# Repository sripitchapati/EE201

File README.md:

# Keerthi Pitchapati
## About Me

Hi! My name is Sri Keerthi Pitchapati. I am currently a junior studying Electrical and Computer Engineering. 
Apart from this class, I'm taking EE 242, EE 215, CEE 291, and Engr 321. In this class, I'm most excited to 
learn things that I feel will be incredibly applicable to anything that I will do in the future

Apart from school, I have an internship with a company called Slice. Slice is a pizza delivery place that focuses 
local pizzerias, and giving them a platform to sell pizza online. 

Some of my hobbies include going to the gym, skiing, and reading. I ski almost every weekend and I enjoy meeting people
with this shared interest. In addition, I go to the gym almost every day. I also read often and enjoy science fiction.

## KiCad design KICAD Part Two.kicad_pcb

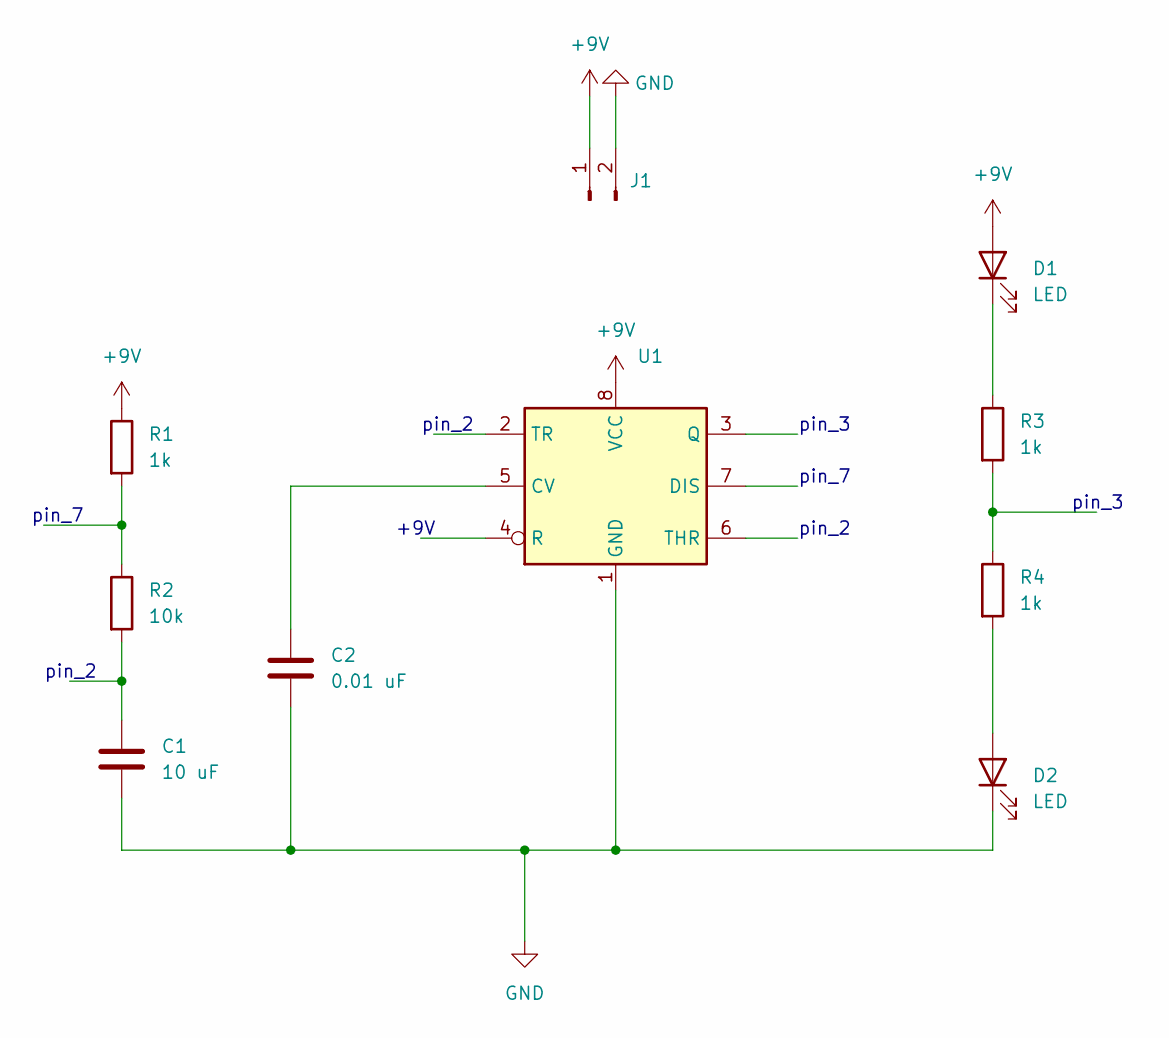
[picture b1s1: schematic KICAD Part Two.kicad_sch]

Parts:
C1: 10 uF; CP_EIA-3216-18_Kemet-A_Pad1.58x1.35mm_HandSolder
C2: 0.01 uF; C_0805_2012Metric_Pad1.18x1.45mm_HandSolder
D1, D2: LED; LED_1206_3216Metric_Pad1.42x1.75mm_HandSolder
J1: TerminalBlock_bornier-2_P5.08mm
R1, R3, R4: 1k; R_0805_2012Metric_Pad1.20x1.40mm_HandSolder
R2: 10k; R_0805_2012Metric_Pad1.20x1.40mm_HandSolder
U1: SOIC-8-1EP_3.9x4.9mm_P1.27mm_EP2.29x3mm

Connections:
+9V: D1.2 (A), J1.1, R1.1, U1.8 (VCC)
GND: C1.2, C2.2, D2.1 (K), J1.2, U1.1 (GND)
unnamed: C1.1, R2.2
unnamed: C2.1, U1.5 (CV)
unnamed: D2.2 (A), R4.2
unnamed: R1.2, R2.1
unnamed: D1.1 (K), R3.1
unnamed: R3.2, R4.1

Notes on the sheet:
+9V
pin_2
pin_3
pin_7
pin_7

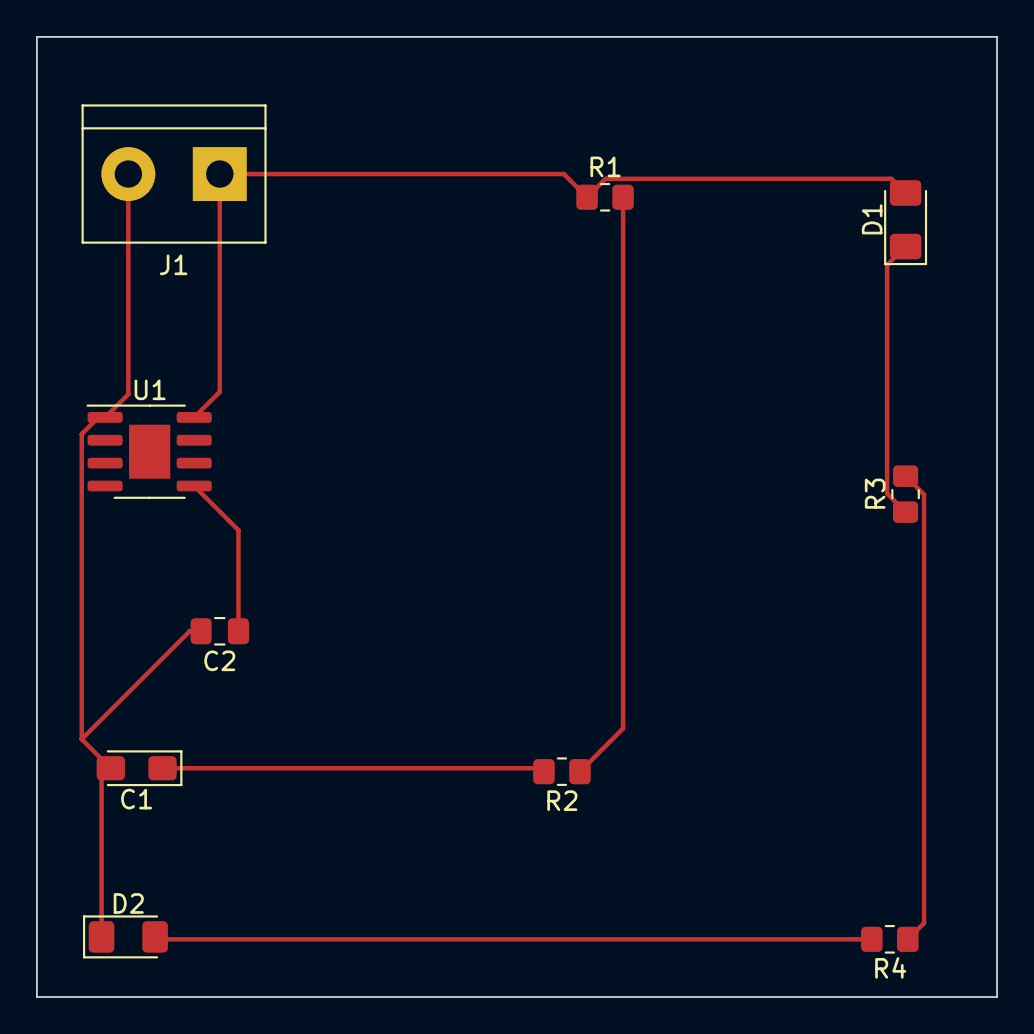
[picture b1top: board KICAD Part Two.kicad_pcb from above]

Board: 2 copper layers, 53.3 x 53.3 mm, 10 parts (0 on the bottom side), 8 nets.

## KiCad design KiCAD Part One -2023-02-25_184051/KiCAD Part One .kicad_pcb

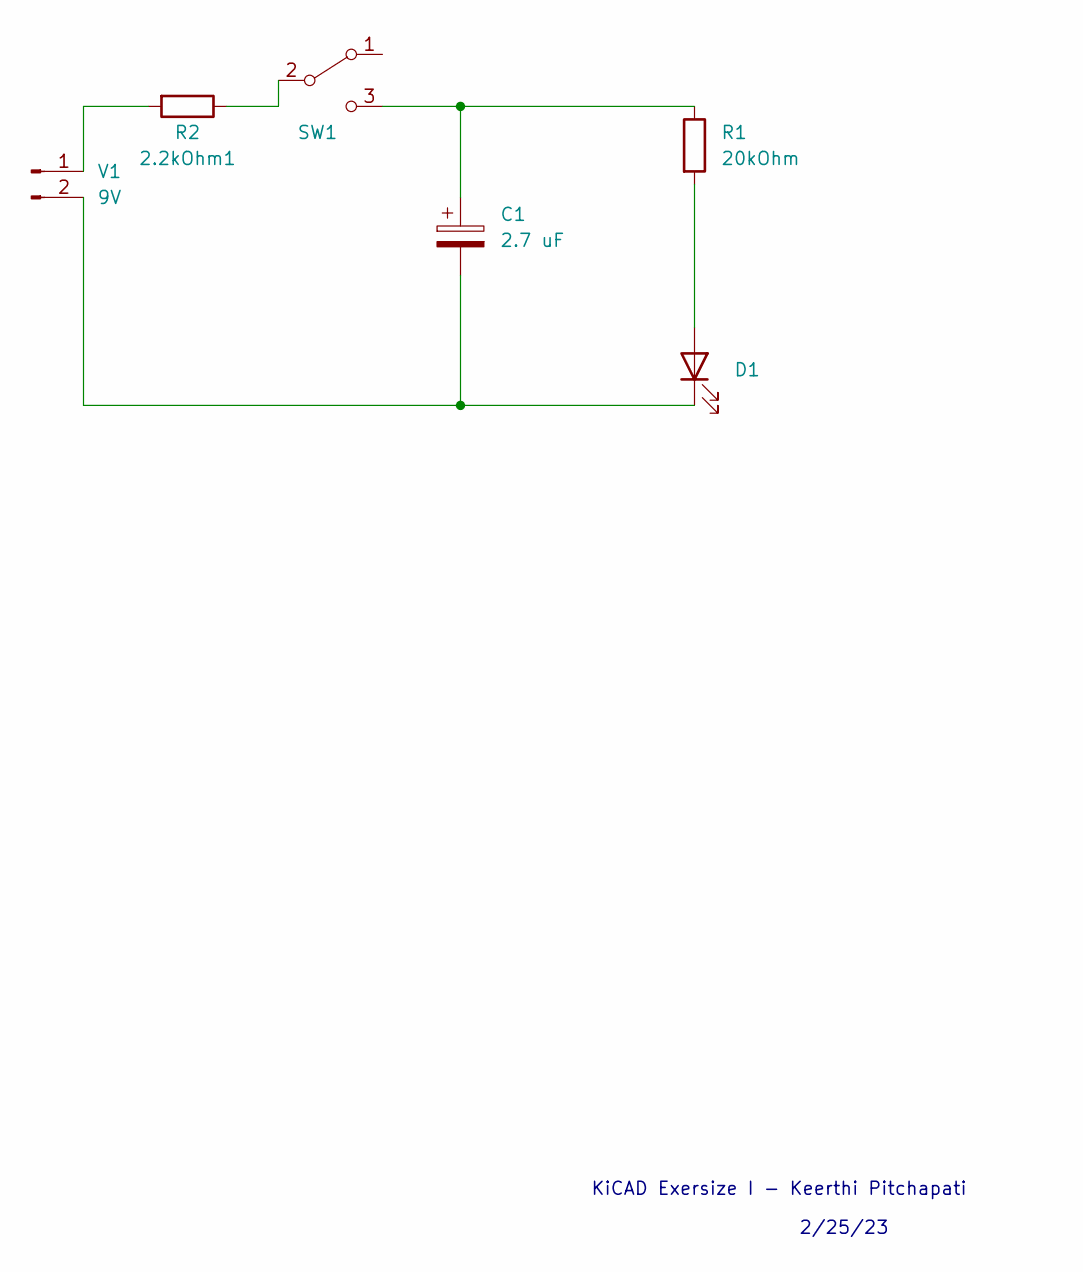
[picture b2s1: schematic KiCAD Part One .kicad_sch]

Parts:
2.2kOhm1: R2; R_Axial_DIN0516_L15.5mm_D5.0mm_P20.32mm_Horizontal
C1: 2.7 uF; C_Radial_D5.0mm_H5.0mm_P2.00mm
D1: LED_D5.0mm
R1: 20kOhm; R_Axial_DIN0516_L15.5mm_D5.0mm_P20.32mm_Horizontal
SW1: SW_E-Switch_EG1224_SPDT_Angled
V1: 9V; JST_PH_B2B-PH-K_1x02_P2.00mm_Vertical

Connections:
unnamed: 2.2kOhm1.1, SW1.2 (B)
unnamed: 2.2kOhm1.2, V1.1
unnamed: C1.1, R1.1, SW1.3 (C)
unnamed: C1.2, D1.1 (K), V1.2
unnamed: D1.2 (A), R1.2

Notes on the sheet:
KiCAD Exersize I - Keerthi Pitchapati
2/25/23

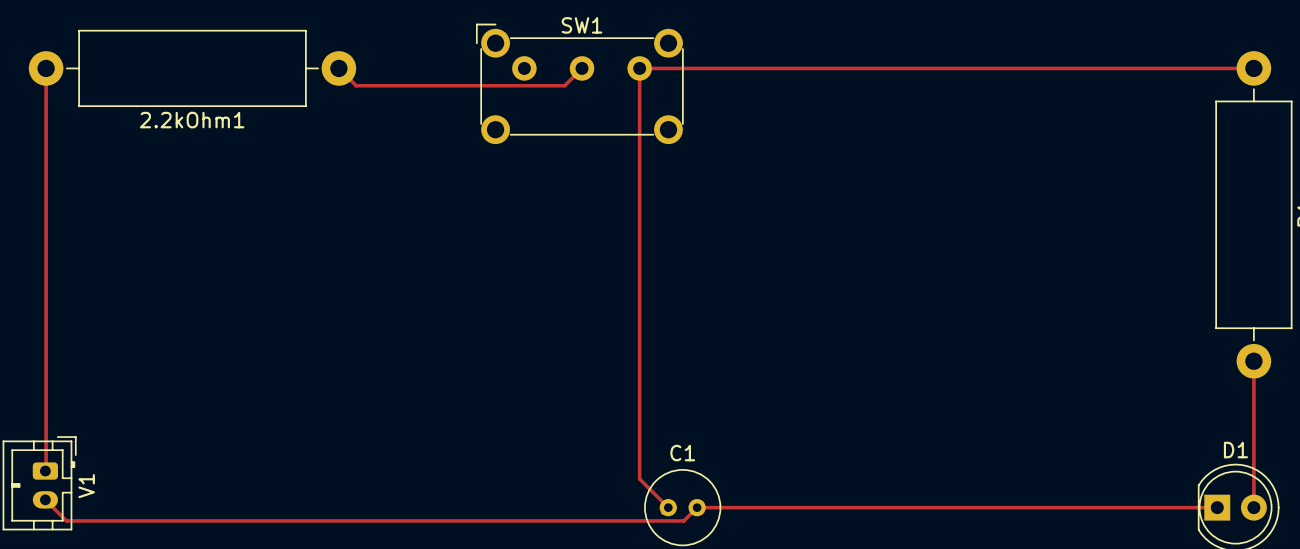
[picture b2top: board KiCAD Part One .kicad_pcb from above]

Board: 2 copper layers, 6 parts (0 on the bottom side), 5 nets.

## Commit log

2023-02-22 Arduino Assignment Lab 3
2023-02-26 kicad part one
2023-03-02 EE 201 GerberFile
2023-03-09 arduino part two
2023-03-10 Arduino Resubmission
2023-03-10 KiCAD Resubmission
2023-03-10 Attached are pictures of the demo
